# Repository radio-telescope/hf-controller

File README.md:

HF controller
=============

TODO

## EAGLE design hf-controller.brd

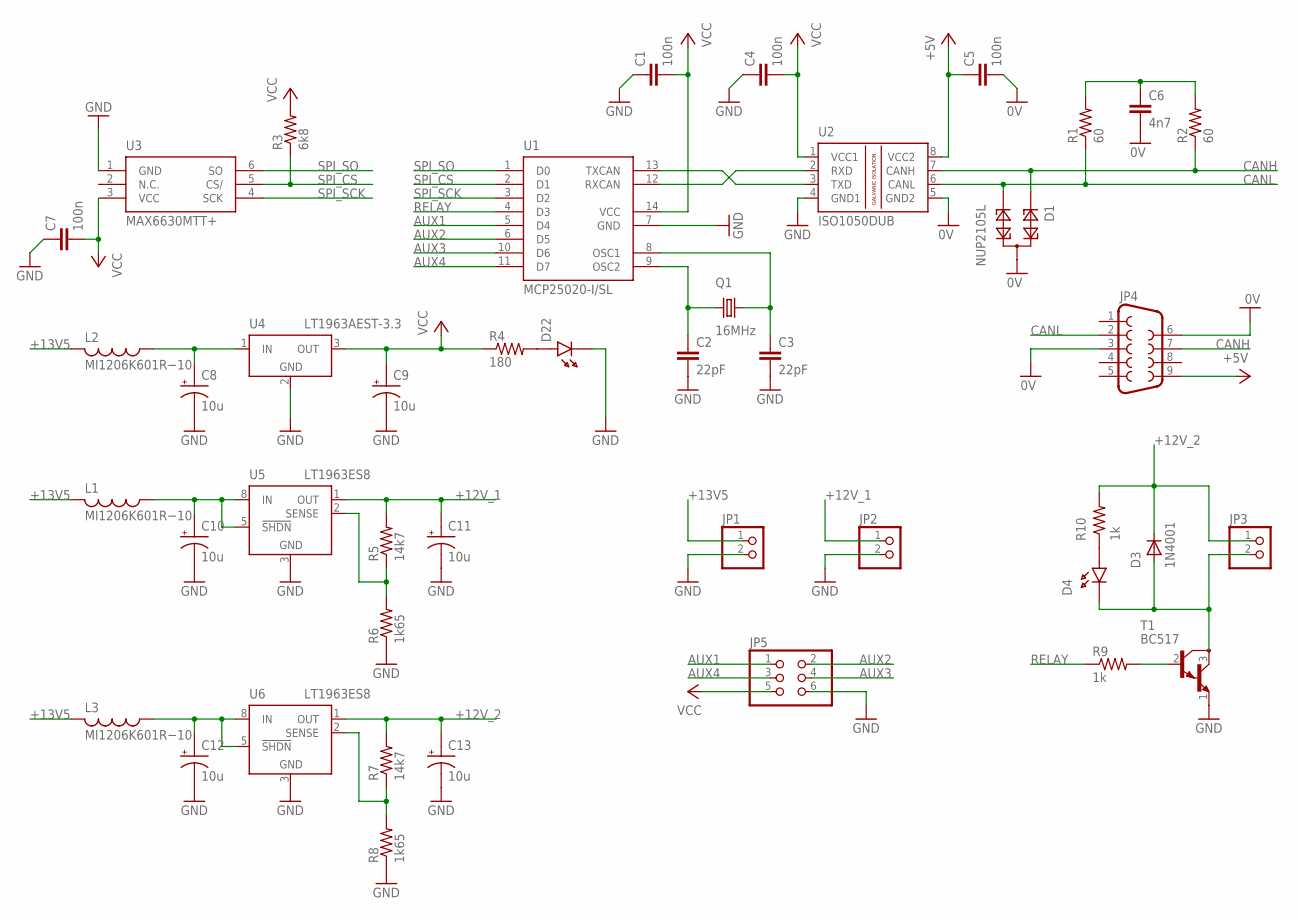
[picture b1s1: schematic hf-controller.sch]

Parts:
C1, C4, C5, C7: 100n; C0805
C2, C3: 22pF; C0805
C6: 4n7; C0805
C8, C9, C10, C11, C12, C13: 10u; CAPACITOR_POL_1210
D1: NUP2105L; SOT23
D3: 1N4001; DO41-10
D4, D22: LED; LED_1206
JP1, JP2, JP3: PINHD-1X2; 1X02
JP4: F09HP
JP5: PINHD-2X3; 2X03
L1, L2, L3: MI1206K601R−10; L3216C
Q1: 16MHz; HC49/S
R1, R2: 60; M0805
R3: 6k8; R0805
R4: 180; R0805
R5, R7: 14k7; R0805
R6, R8: 1k65; R0805
R9: 1k; R0805
R10: 1k; R1206
T1: BC517; TO92
U1: MCP25020-I/SL; MCP25050
U2: ISO1050DUB; DUB-R-PDSO-G8
U3: MAX6630MTT+
U4: LT1963AEST-3.3; SOT223
U5, U6: LT1963ES8; SOIC8

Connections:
0V: C5.2, C6.2, D1.3, JP4.3, JP4.6, U2.5 (GND2)
+5V: C5.1, JP4.9, U2.8 (VCC2)
+12V_1: C11.A, JP2.1, R5.2, U5.1 (OUT)
+12V_2: C13.A, D3.C, JP3.1, R7.2, R10.2, U6.1 (OUT)
+13V5: JP1.1, L1.2, L2.2, L3.2
AUX1: JP5.1, U1.5 (D4)
AUX2: JP5.2, U1.6 (D5)
AUX3: JP5.4, U1.10 (D6)
AUX4: JP5.3, U1.11 (D7)
CANH: D1.1, JP4.7, R2.1, U2.7 (CANH)
CANL: D1.2, JP4.2, R1.1, U2.6 (CANL)
GND: C1.1, C2.2, C3.2, C4.1, C7.1, C8.C, C9.C, C10.C, C11.C, C12.C, C13.C, D22.C, JP1.2, JP2.2, JP5.6, R6.1, R8.1, T1.1 (E), U1.7 (GND), U2.4 (GND1), U3.1 (GND), U4.2 (GND), U4.4 (GND), U5.3 (GND), U5.6 (GND), U5.7 (GND), U6.3 (GND), U6.6 (GND), U6.7 (GND)
unnamed: U1.13 (TXCAN), U2.3 (TXD)
unnamed: U1.12 (RXCAN), U2.2 (RXD)
unnamed: C2.1, Q1.1, U1.9 (OSC2)
unnamed: C3.1, Q1.2, U1.8 (OSC1)
unnamed: C10.A, L1.1, U5.5 (!SHDN), U5.8 (IN)
unnamed: R9.2, T1.2 (B)
unnamed: C12.A, L3.1, U6.5 (!SHDN), U6.8 (IN)
unnamed: C6.1, R1.2, R2.2
unnamed: C8.A, L2.1, U4.1 (IN)
unnamed: D3.A, D4.C, JP3.2, T1.3 (C)
unnamed: R7.1, R8.2, U6.2 (SENSE)
unnamed: R5.1, R6.2, U5.2 (SENSE)
unnamed: D22.A, R4.2
unnamed: D4.A, R10.1
RELAY: R9.1, U1.4 (D3)
SPI_CS: R3.1, U1.2 (D1), U3.5 (CS/)
SPI_SCK: U1.3 (D2), U3.4 (SCK)
SPI_SO: U1.1 (D0), U3.6 (SO)
VCC: C1.2, C4.2, C7.2, C9.A, JP5.5, R3.2, R4.1, U1.14 (VCC), U2.1 (VCC1), U3.3 (VCC), U4.3 (OUT)

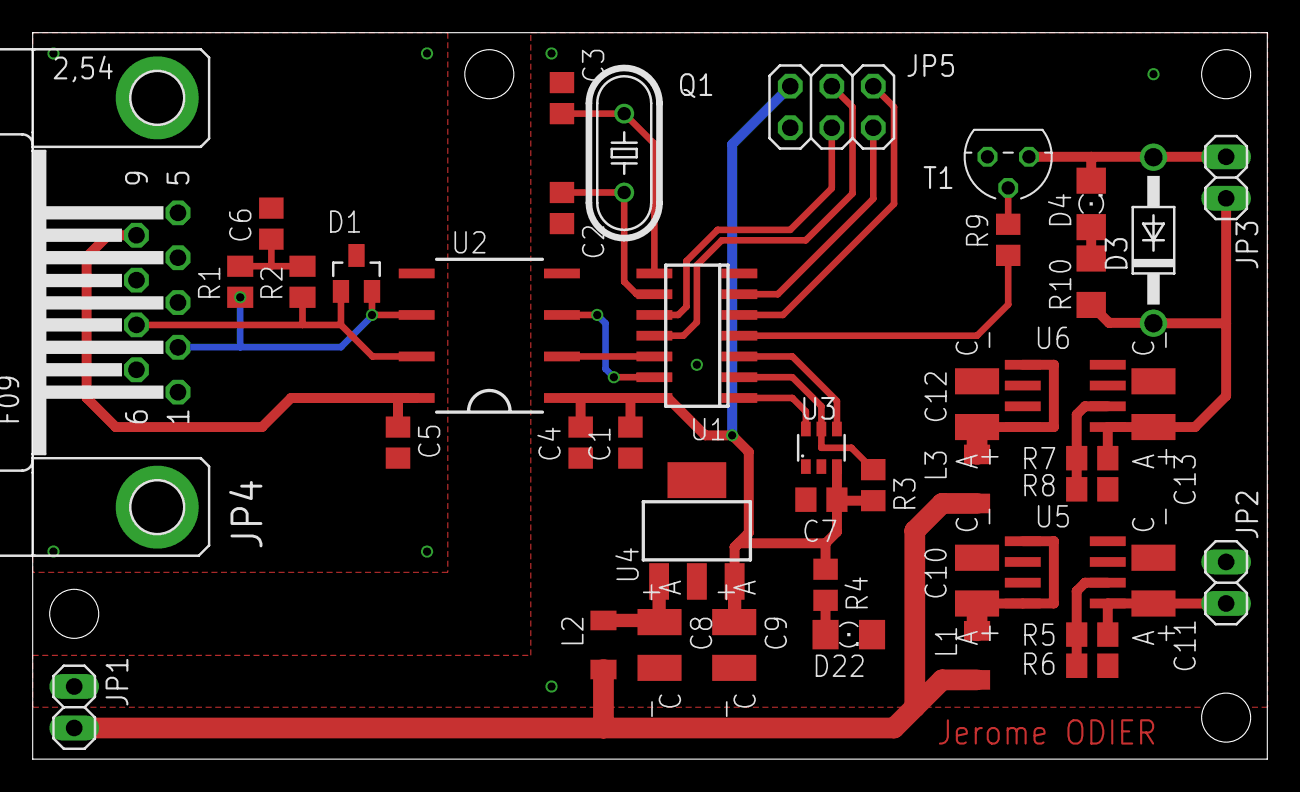
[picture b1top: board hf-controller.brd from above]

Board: 2 copper layers, 75.5 x 44.5 mm, 43 parts (0 on the bottom side), 31 nets.
